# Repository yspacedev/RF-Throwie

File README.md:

## About
The RF throwie is an ultra-cheap sub-GHz transmitter using the CMOSTek/HopeRF $1 CMT2119A RF transmitter and $0.10 CH32V003 32-bit RISC-V microcontroller on a 20x20mm 2-layer board.

Called a "throwie" because it's designed to be cheap enough (almost disposable) that you can throw it anywhere for a foxhunt or other RF application.

The CMT2119A supports (G)FSK/OOK modulation and a tuning range of 157MHz - 1297MHz (according to G4EML). While it's meant to be configured with CMOSTek's RFPDK and their proprietary software, it can be configured in-situ though a 2-wire interface that writes to registers on the chip. The registers have been partly reverse engineered in https://github.com/g4eml/RP2040_Synth, and this project aims to reverse engineer them more fully to allow for full customization without the RFPDK. The CMT2119A can also be used as a general-purpose frequency synthesizer, which opens up a lot of possibilities for cheap SDRs and custom RF frontends. 

### Firmware

The CH32V003 is programmed with cnlohr's ch32fun stack and uses bitbanging to generate the TWI signals. The current firmware transmits Morse code on the UHF ham radio band (70cm band) that can be picked up by an SDR using NBFM demodulation or a cheap handheld transciever like a Baofeng or Quansheng UV-K5. In theory more modulations are possible, including FSK-based modes. However, due to the long (370us) tuning time and coarse frequency resolution (200~400Hz) of the frequency synthesizer, phase modulation through frequency modulation is likely not possible with unmodified hardware. Maybe using a bitstream to generate harmonics and then filtering before feeding into the reference oscillator input could result in a fine frequency resolution on inexpensive hardware, but this has yet to be tested.

For development and compilation, you will need to set up CH32fun per the instructions on their github. If you use clangd or Microsoft Intellisense with VSCode/VSCodium, those options are already set up, but you will need to change the path for the libraries or use `compiledb make` to generate the `compile_commands.json` file.

### Board/hardware

The RF throwie board itself supports an input voltage of 3.7v - 18v, and has an onboard LED and the CH32V003 UART interface exposed. There are also 2 jumpers on the back that connect the UART pins to the CMT2119A TWI pins to turn it into a breakout board. For the RF chip, there's a up to 7th order LC filter and matching network feeding an SMA connector or simple wire antenna.

## Tuning

The RF output pin has a frequency dependent impedance, and since CMOSTek only provided the impedance at 4 test frequencies, I used a Python curve fitter to get an empirical equation for the output impedance. This Desmos graph implements the formula: https://www.desmos.com/calculator/a3xyh0sjgi

To create a custom matching network for the transmitter, use https://home.sandiego.edu/~ekim/e194rfs01/jwmatcher/matcher2.html to create a match to 50 ohms and then use https://markimicrowave.com/technical-resources/tools/lc-filter-design-tool/ to generate a filter network.

## Extra Information

Extra information like LCSC part numbers for certain components is included in the KiCAD schematic.

It's designed to be fabricated on a 1.6mm FR4 2 layer board.

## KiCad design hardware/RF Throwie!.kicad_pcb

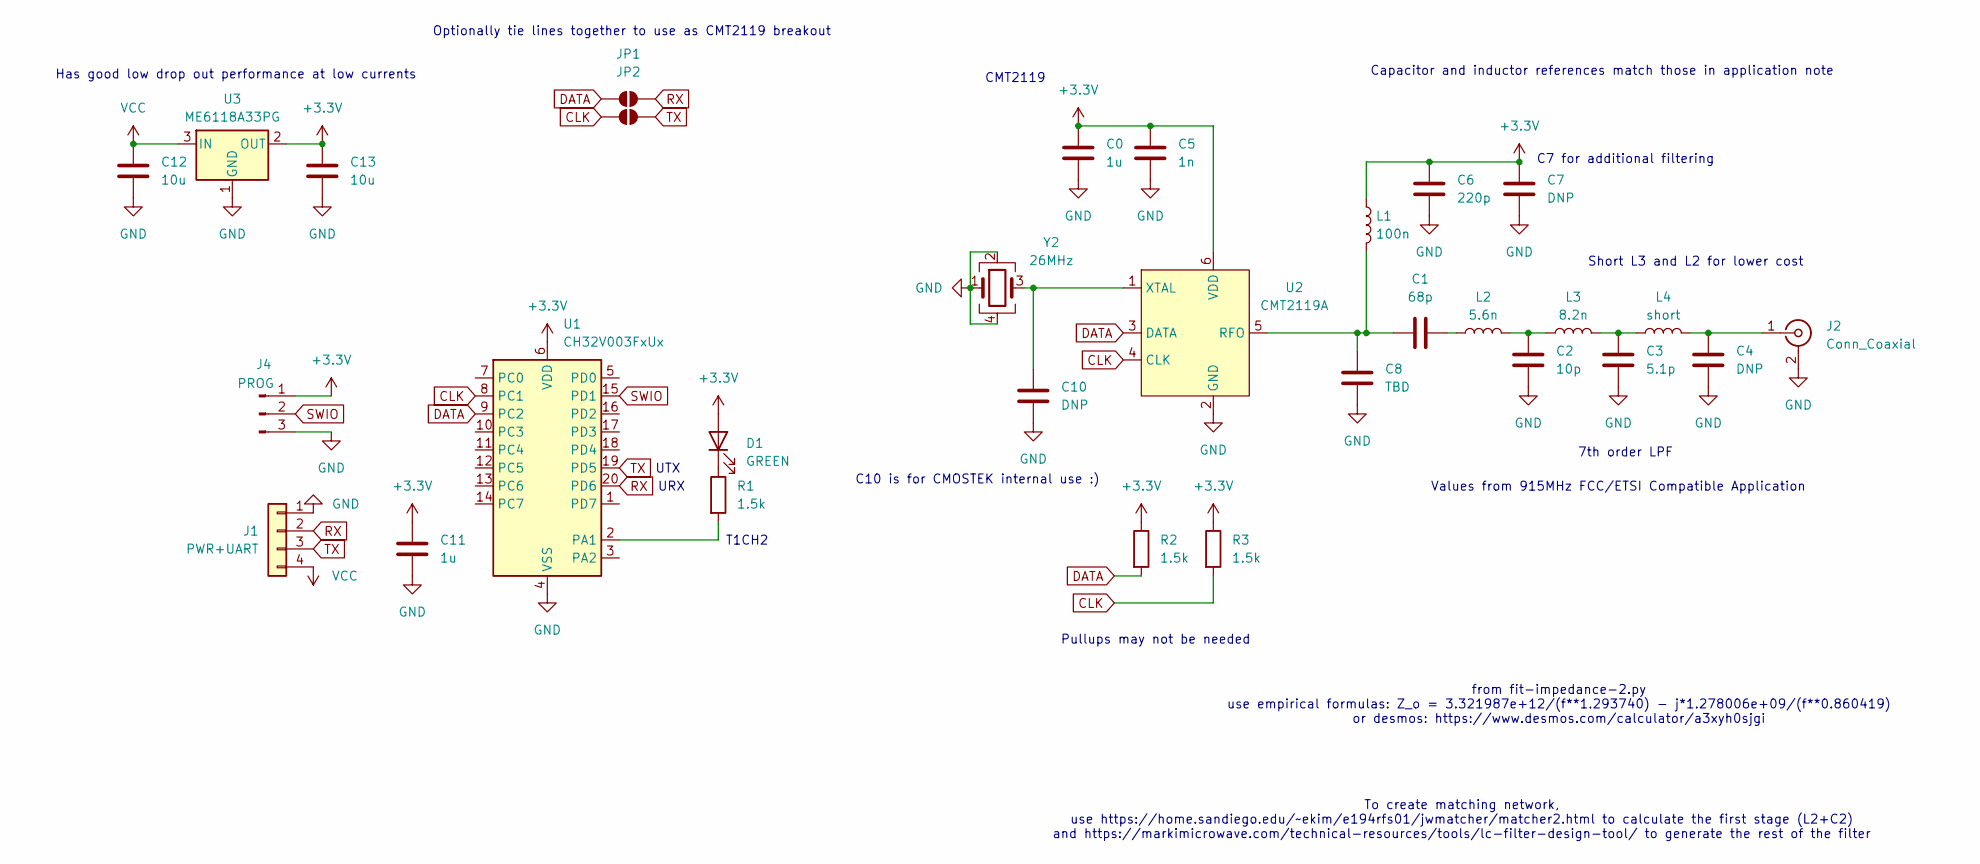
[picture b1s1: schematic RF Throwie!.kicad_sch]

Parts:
C0, C11: 1u; C_0402_1005Metric
C1: 68p; C_0402_1005Metric
C2: 10p; C_0402_1005Metric
C3: 5.1p; C_0402_1005Metric
C4, C7, C10: DNP; C_0402_1005Metric
C5: 1n; C_0402_1005Metric
C6: 220p; C_0402_1005Metric
C8: TBD; C_0402_1005Metric
C12, C13: 10u; C_1206_3216Metric
D1: GREEN; LED_0603_1608Metric
J1: PWR+UART; PinHeader_1x04_P2.54mm_Vertical
J2: Conn_Coaxial; SMA_Samtec_SMA-J-P-H-ST-EM1_EdgeMount
J4: PROG; JST_SH_SM03B-SRSS-TB_1x03-1MP_P1.00mm_Horizontal
JP1, JP2: SolderJumper_2_Open; SolderJumper-2_P1.3mm_Open_RoundedPad1.0x1.5mm
L1: 100n; L_0603_1608Metric
L2: 5.6n; L_0603_1608Metric
L3: 8.2n; L_0603_1608Metric
L4: short; L_0603_1608Metric
R1, R2, R3: 1.5k; R_0402_1005Metric
U1: CH32V003FxUx; QFN-20-1EP_3x3mm_P0.4mm_EP1.65x1.65mm; LCSC Part Number C5299908
U2: CMT2119A; SOT-23-6; LCSC Part Number C77214
U3: ME6118A33PG; SOT-89-3; LCSC Part Number C236721
Y2: 26MHz; Crystal_SMD_2016-4Pin_2.0x1.6mm; LCSC Part Number C2933002

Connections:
+3.3V: C0.1, C5.1, C6.1, C7.1, C11.1, C13.1, D1.2 (A), J4.1, L1.1, R2.1, R3.1, U1.6 (VDD), U2.6 (VDD), U3.2 (OUT)
CLK: JP2.1 (A), R3.2, U1.8 (PC1), U2.4 (CLK)
DATA: JP1.1 (A), R2.2, U1.9 (PC2), U2.3 (DATA)
GND: C0.2, C2.2, C3.2, C4.2, C5.2, C6.2, C7.2, C8.2, C10.2, C11.2, C12.2, C13.2, J1.1, J2.2 (Ext), J4.3, U1.4 (VSS), U1.21 (VSS), U2.2 (GND), U3.1 (GND), Y2.1, Y2.2, Y2.4
unnamed: C1.2, L2.1
unnamed: C2.1, L2.2, L3.1
unnamed: C3.1, L3.2, L4.1
unnamed: D1.1 (K), R1.1
unnamed: C4.1, J2.1 (In), L4.2
unnamed: R1.2, U1.2 (PA1)
unnamed: C1.1, C8.1, L1.2, U2.5 (RFO)
unnamed: C10.1, U2.1 (XTAL), Y2.3
RX: J1.2, JP1.2 (B), U1.20 (PD6)
SWIO: J4.2, U1.15 (PD1)
TX: J1.3, JP2.2 (B), U1.19 (PD5)
VCC: C12.1, J1.4, U3.3 (IN)

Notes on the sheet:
CMT2119
C10 is for CMOSTEK internal use :)
Pullups may not be needed
7th order LPF
Capacitor and inductor references match those in application note
URX
Has good low drop out performance at low currents
UTX
T1CH2
To create matching network, use https://home.sandiego.edu/~ekim/e194rfs01/jwmatcher/matcher2.html to calculate the first stage (L2+C2) and https://markimicrowave.com/technical-resources/tools/lc-filter-design-tool/ to generate the rest of the filter
C7 for additional filtering
Short L3 and L2 for lower cost
Optionally tie lines together to use as CMT2119 breakout
Values from 915MHz FCC/ETSI Compatible Application
from fit-impedance-2.py use empirical formulas: Z_o = 3.321987e+12/(f**1.293740) - j*1.278006e+09/(f**0.860419) or desmos: https://www.desmos.com/calculator/a3xyh0sjgi

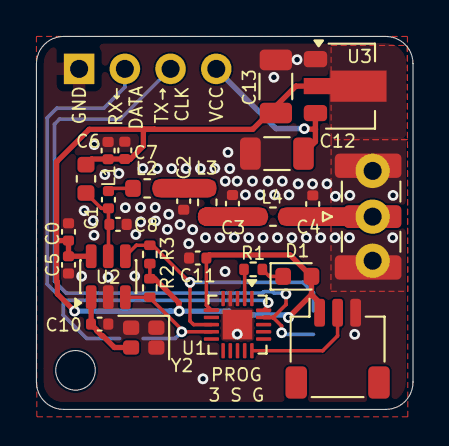
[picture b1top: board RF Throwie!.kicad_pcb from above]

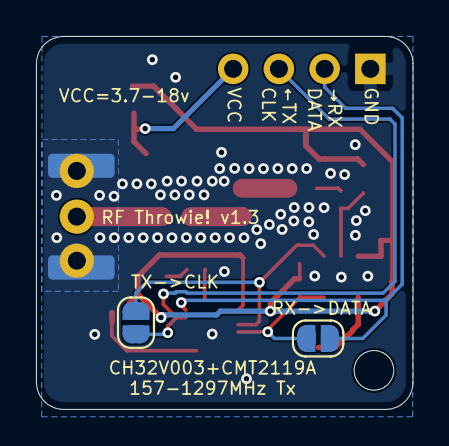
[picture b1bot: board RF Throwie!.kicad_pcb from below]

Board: 2 copper layers, 20.9 x 20.7 mm, 30 parts (2 on the bottom side), 16 nets.

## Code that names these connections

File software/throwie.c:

#include "ch32fun.h"
#include "CMT2119A.h"
#include "CMT2119A_TWI.h"
#include "ch32v003hw.h"

#define TONE_HZ 1000
#define CTR_RELOAD (2000000/TONE_HZ)
#define MORSE_WPM 20
//50 units in the word "PARIS"
//50*WPM is the number of units per minute (1/(50*WPM))*MS_PER_MINUTE
#define MORSE_UNIT_MS ((60*1000)/(50*MORSE_WPM))

const char* morse_string = "CALLSIGN TEST"; //replace with your own callsign or change TX_FREQ to an ISM band

//possibly rearrange to map better onto ascii
const char* MORSE_ALPHABET[] = {
    ".-",   // A
    "-...", // B
    "-.-.", // C
    "-..",  // D
    ".",    // E
    "..-.", // F
    "--.",  // G
    "....", // H
    "..",   // I
    ".---", // J
    "-.-",  // K
    ".-..", // L
    "--",   // M
    "-.",   // N
    "---",  // O
    ".--.", // P
    "--.-", // Q
    ".-.",  // R
    "...",  // S
    "-",    // T
    "..-",  // U
    "...-", // V
    ".--",  // W
    "-..-", // X
    "-.--", // Y
    "--..", // Z
	"-----",// 0
	".----",// 1
	"..---",// 2
	"...--",// 3
	"....-",// 4
	".....",// 5
	"-....",// 6
	"--...",// 7
	"---..",// 8
	"----.",// 9
};

char upper(char c){
	if (c>='a' && c<='z'){
		return c - 20;
	}
	return c;
}

uint8_t morse_lookup(char c){
	uint8_t idx = 0;
	char up_char = (char)upper((int)c);
	if (up_char >= '0' && up_char <= '9') {
		idx=up_char-'0'+26;
	} else if (up_char >= 'A' && up_char <= 'Z'){
		idx=up_char-'A';
	}
	return idx;
}

void morse_char(char char_in){
	if (char_in==' '){
		Delay_Ms(6*MORSE_UNIT_MS); //6 units instead of 7 since 1 unit delay comes after every dit or dah
		return;
	}
	uint8_t idx = morse_lookup(char_in);
	
	if (idx>=(sizeof(MORSE_ALPHABET)/sizeof(char*))) return;
	char* code = (char*)MORSE_ALPHABET[idx];
	char c = *code;
	while (c!=0){
		int sym = 1;
		if (c=='.'){
			sym=1;
		} else if (c=='-') {
			sym=3;
		}
		funPinMode(TWIDAT, GPIO_Speed_10MHz | GPIO_CNF_OUT_PP_AF); //switch to timer output
		TIM2->CTLR1 |= TIM_CEN; //enable timer
		Delay_Ms(sym*MORSE_UNIT_MS);
		TIM2->CTLR1 &= ~TIM_CEN; //disable timer
		funPinMode(TWIDAT, FUN_OUTPUT); //switch back to GPIO
		TWI_DAT_HIGH //keep high to prevent transmitter going into sleep mode

		code++;
		c=*code;
		Delay_Ms(1*MORSE_UNIT_MS);
	}
	Delay_Ms(2*MORSE_UNIT_MS);
}

void encode_morse(const char *str){
	char c = *str;
	while (c!=0){
		morse_char(c);
		str++;
		c=*str;
	}
}

//use a timer to modulate the FSK into a continuous tone
void init_tone_timer(void){
	//PC2 has alternate remapping to T2CH2

	//enable AFIO and TIM2
	RCC->APB2PCENR |= RCC_APB2Periph_AFIO | RCC_APB2Periph_GPIOC;
	RCC->APB1PCENR |= RCC_APB1Periph_TIM2;

	//remap alternate function
	AFIO->PCFR1 |= AFIO_PCFR1_TIM2_REMAP_PARTIALREMAP1;

	//reset TIM2
	RCC->APB1PRSTR |= RCC_APB1Periph_TIM2;
	RCC->APB1PRSTR &= ~RCC_APB1Periph_TIM2;

	//Set prescaler
	TIM2->PSC = 23; //divide by 24
	
	TIM2->ATRLR = CTR_RELOAD;

	TIM2->CHCTLR1 |= TIM_OC2M_2 | TIM_OC2M_1 | TIM_OC2PE;

	TIM2->CH2CVR = CTR_RELOAD/2;

	TIM2->CTLR1 |= TIM_ARPE;

	TIM2->CCER |= TIM_CC2E | TIM_CC2P;

	TIM2->SWEVGR |= TIM_UG; //initialize counter
}


#define LED PA1
#define UART_TX PD5
#define UART_RX PD6

int main(){
	SystemInit();

	funGpioInitAll(); // Enable GPIOs
	init_tone_timer();
	funPinMode(LED, FUN_OUTPUT);
	funPinMode(PC2, GPIO_Speed_10MHz | GPIO_CNF_OUT_PP_AF);

	CMT2119A_settings_t tx_settings = {
		.freq_out_hz = 430100000,
		.fsk_dev_hz = 2000,
		.gfsk_rate_bps = 1600, //minimum required for 1khz tone in GFSK mode
		.power_output_dbm = -10,
		.modulation = MOD_FSK,
		.off_time = OFF_90MS,
		.pa_ramp_time = 0,
		.edge_start = EDGE_RISING,
		.invert_symbols = false,
		.xo_current_boost = false,
	};

	CMT2119A_init(PC1, PC2, &tx_settings); //use default frequency

	while(1)
	{
		funDigitalWrite(LED, FUN_LOW);
		//CMT2119A_update(); 
		//frequency can also be changed live, but transmitting the PLL parameters takes more time if we don't need to do so
		TWI_reset();
		Delay_Ms(2);
		CMT2119A_TWI_OFF();
		TWI_DAT_HIGH //wake up from sleep mode
		Delay_Us(1);
		TWI_DAT_LOW
		encode_morse(morse_string);
		TWI_reset(); //turns transmitter off
		//to transmit continuously, leave the DAT pin high
		funDigitalWrite(LED, FUN_HIGH);
		Delay_Ms(1000);
	}
}

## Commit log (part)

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2025-11-12 Initial Commit!
2025-11-12 Add PDF schematic
2025-11-13 Add RX->DATA and TX->CLK jumpers, add more helpful silkscreen, fix SMA connector footprint
